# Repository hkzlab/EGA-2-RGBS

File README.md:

# EGA-2-RGBS

Months ago I ran into [this](https://www.youtube.com/watch?v=vwKA1z8tg1g&t=527) video on YouTube that described how to implement an EGA/CGA to analog RGBS signal using just a ROM and a few passive components.
Thinking it was a nice idea, I decided to implement my variant of it (including the tool that generates the values to program the EPROM), also including an optional buffer on the outputs of the ROM.

**CAVEAT EMPTOR:** For now I tested this board only in DOS with a CGA card. Will update this note when I test EGA and colours.

Note that this **will not convert EGA/CGA to VGA**, it will just make the signal analog and compatible with either a SCART input or a scaler like the GBS8200 (tested with [gbs-control](https://github.com/ramapcsx2/gbs-control) firmware).

## Jumpers

- JP1: Bridge if you are using this with an EGA card, remove bridge for CGA
- JP2: Disable Brown colour fix for CGA. No effect on EGA
- JP3: Bridge 1-2 to output a CSYNC signal, bridge 2-3 for /CSYNC

## Building the board

### BOM

- 1x 20pin socket (on U2)
- 1x 32pin wide socket (on U1)
- 2x 100nF ceramic caps (C5 and C4)
- 1x Right angle DB9 female PCB connector (J1)
- 1x 6 or 5 pin screw terminal (J5)
- 1x 2 pin screw terminal (J4)
- 1x 1206 SMD fuse rated around ~100mA (F1), **100mA is already very high for the power consumption of the board, but I had these at hand** 
- 1x 3 pin 2.54mm male pcb header, plus jumper (J3)
- 2x 2 pin 2.54mm male pcb header, plus jumpers (JP1 and JP2)
- 1x First random led you have at hand, optional (D2)
- 1x 1N4733A 5.1v zener diode (D1)
- 1x 74HC244 DIP, optional (U2)
- 1x 27C010 DIP (U1)
- 4x 470 1/4w resistors (R2, R4, R6, R10)
- 3x 1.5k 1/4w resistors (R3, R5, R7)
- 1x 1k 1/4w resistor (R11)
- 2x 4.7k 1/4w resistors (R8, R9)

Remember to program the EPROM with the bin file provided in the repository.

### Building on the cheap

You can omit the following components:

#### Power

Omit F1 and D1, bridge the two connections points of F1. Do this if you trust your power supply and yourself not to make shorts.

You can also omit the power indicator led D2 and its resistor R11

#### Sockets

You can omit both U1 and U2 sockets. Remember to mount C4, C5, R8 and R9 on the underside of the board if you do this.

#### Output buffer

You can omit U2 entirely. Just bridge the following points on the footprint:

- 2->18
- 4->16
- 6->14
- 8->12
- 11->9
- 13->7
- 15->5
- 17->3

Also omit C4 in this case.

## Credits

- [TheRasteri](https://www.youtube.com/channel/UCO1ifHwXHkEyCLFk2b7Z8xA) on YouTube for the original idea

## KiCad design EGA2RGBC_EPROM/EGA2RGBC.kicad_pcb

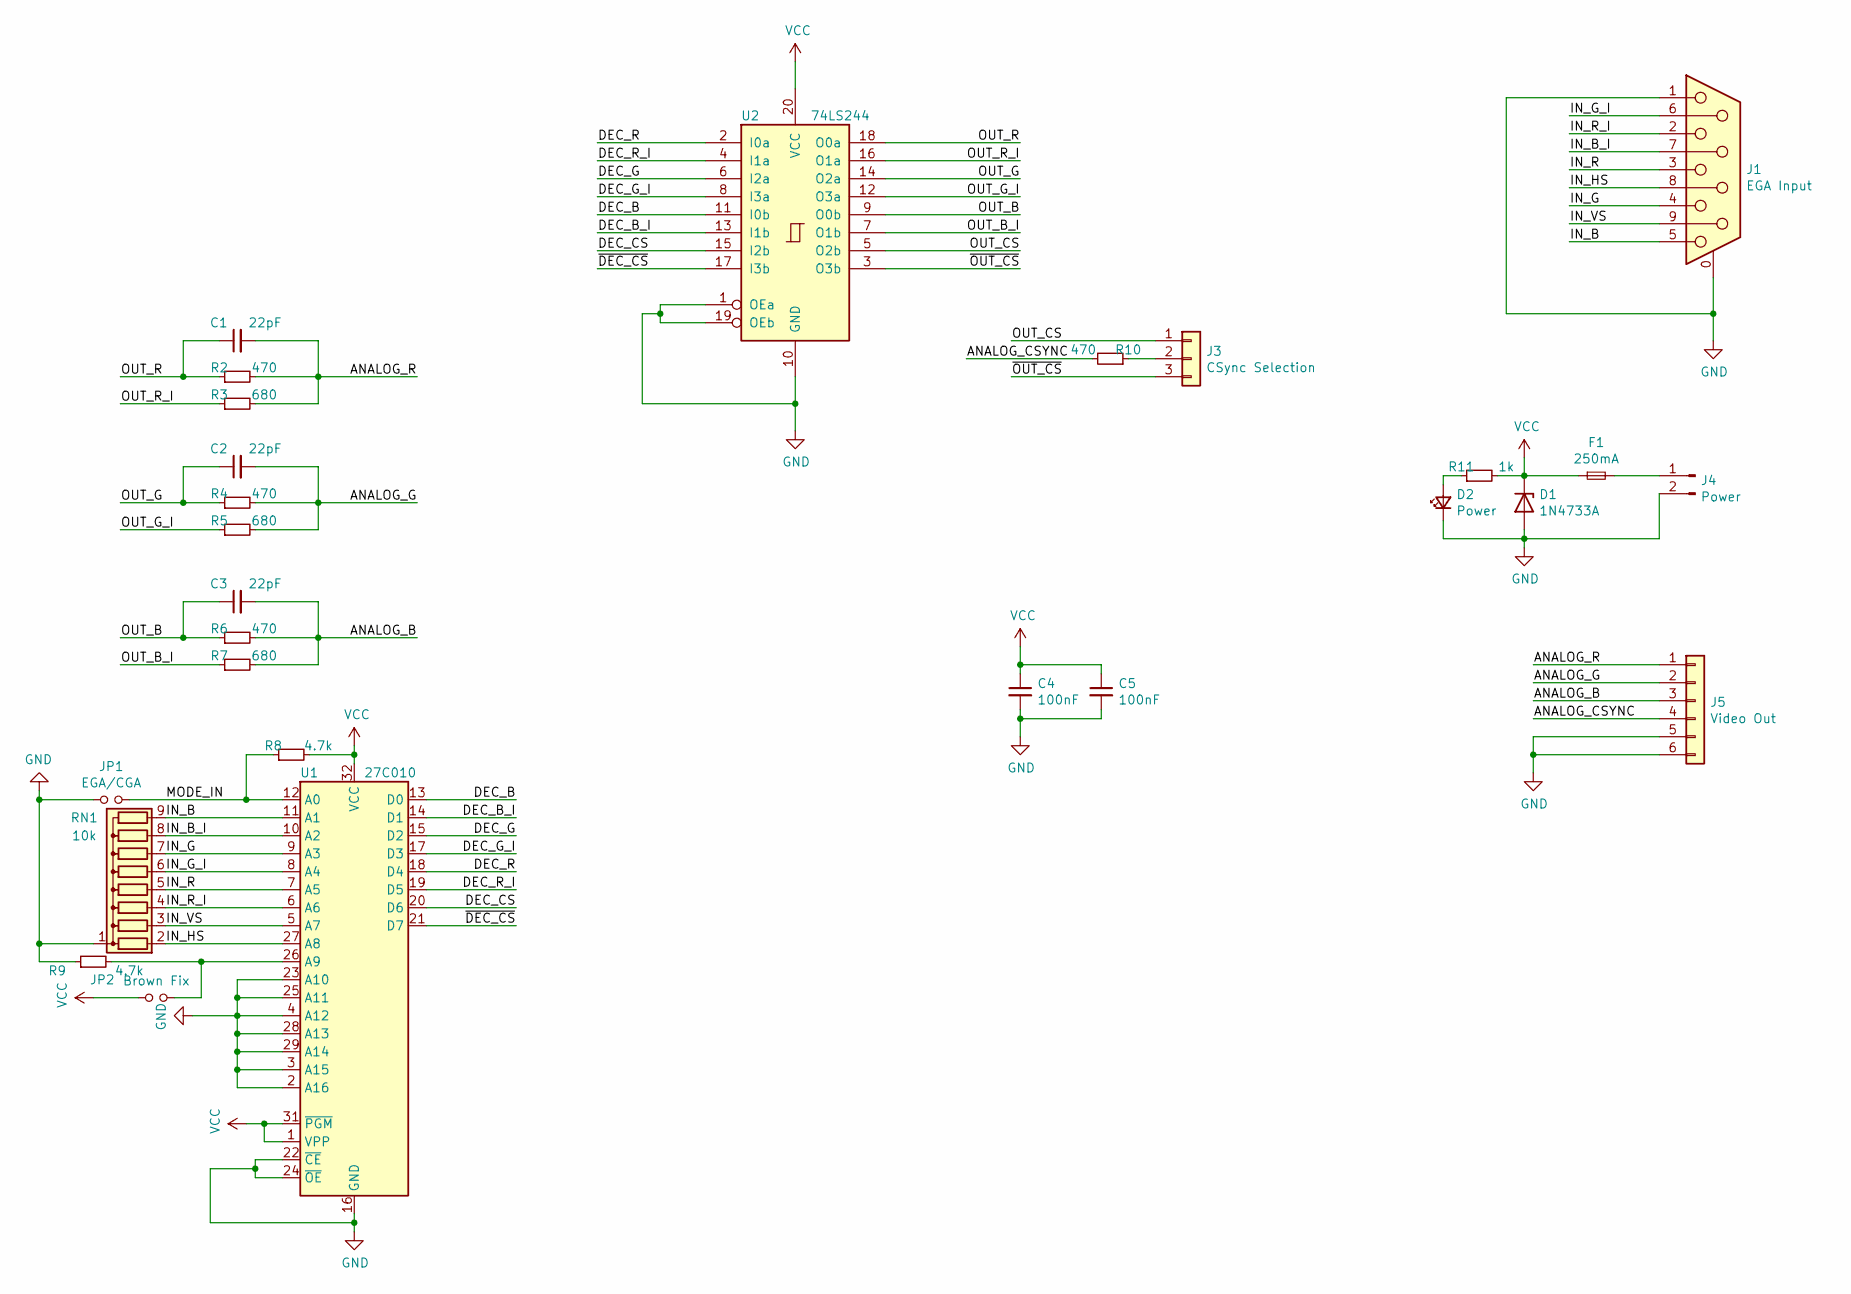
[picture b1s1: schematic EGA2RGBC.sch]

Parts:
C1, C2, C3: 22pF; C_Disc_D3.0mm_W2.0mm_P2.50mm
C4, C5: 100nF; C_Disc_D3.0mm_W2.0mm_P2.50mm
D1: 1N4733A; D_DO-41_SOD81_P10.16mm_Horizontal
D2: Power; LED_D2.0mm_W4.8mm_H2.5mm_FlatTop
F1: 250mA; Fuse_1206_3216Metric
J1: EGA Input; DSUB-9_Female_Horizontal_P2.77x2.84mm_EdgePinOffset4.94mm_H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
J3: CSync Selection; PinSocket_1x03_P2.54mm_Vertical
J4: Power; TerminalBlock_bornier-2_P5.08mm
J5: Video Out; TerminalBlock_bornier-6_P5.08mm
JP1: EGA/CGA; PinHeader_1x02_P2.54mm_Vertical
JP2: Brown Fix; PinHeader_1x02_P2.54mm_Vertical
R2, R4, R6, R10: 470; R_Axial_DIN0204_L3.6mm_D1.6mm_P7.62mm_Horizontal
R3, R5, R7: 680; R_Axial_DIN0204_L3.6mm_D1.6mm_P7.62mm_Horizontal
R8, R9: 4.7k; R_Axial_DIN0204_L3.6mm_D1.6mm_P7.62mm_Horizontal
R11: 1k; R_Axial_DIN0204_L3.6mm_D1.6mm_P7.62mm_Horizontal
RN1: 10k; R_Array_SIP9
U1: 27C010; DIP-32_W15.24mm
U2: 74LS244; DIP-20_W7.62mm

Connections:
/ANALOG_B: C3.2, J5.3, R6.2, R7.2
/ANALOG_CSYNC: J5.4, R10.2
/ANALOG_G: C2.2, J5.2, R4.2, R5.2
/ANALOG_R: C1.2, J5.1, R2.2, R3.2
/DEC_B: U1.13 (D0), U2.11 (I0b)
/DEC_B_I: U1.14 (D1), U2.13 (I1b)
/DEC_CS: U1.20 (D6), U2.15 (I2b)
/DEC_G: U1.15 (D2), U2.6 (I2a)
/DEC_G_I: U1.17 (D3), U2.8 (I3a)
/DEC_R: U1.18 (D4), U2.2 (I0a)
/DEC_R_I: U1.19 (D5), U2.4 (I1a)
/IN_B: J1.5, RN1.9 (R8), U1.11 (A1)
/IN_B_I: J1.7, RN1.8 (R7), U1.10 (A2)
/IN_G: J1.4, RN1.7 (R6), U1.9 (A3)
/IN_G_I: J1.6, RN1.6 (R5), U1.8 (A4)
/IN_HS: J1.8, RN1.2 (R1), U1.27 (A8)
/IN_R: J1.3, RN1.5 (R4), U1.7 (A5)
/IN_R_I: J1.2, RN1.4 (R3), U1.6 (A6)
/IN_VS: J1.9, RN1.3 (R2), U1.5 (A7)
/MODE_IN: JP1.2, R8.1, U1.12 (A0)
/OUT_B: C3.1, R6.1, U2.9 (O0b)
/OUT_B_I: R7.1, U2.7 (O1b)
/OUT_CS: J3.1, U2.5 (O2b)
/OUT_G: C2.1, R4.1, U2.14 (O2a)
/OUT_G_I: R5.1, U2.12 (O3a)
/OUT_R: C1.1, R2.1, U2.18 (O0a)
/OUT_R_I: R3.1, U2.16 (O1a)
/~DEC_CS: U1.21 (D7), U2.17 (I3b)
/~OUT_CS: J3.3, U2.3 (O3b)
GND: C4.2, C5.2, D1.2 (A), D2.1 (K), J1.0 (PAD), J1.1, J4.2, J5.5, J5.6, JP1.1, R9.1, RN1.1 (common), U1.2 (A16), U1.3 (A15), U1.4 (A12), U1.16 (GND), U1.22 (~CE), U1.23 (A10), U1.24 (~OE), U1.25 (A11), U1.28 (A13), U1.29 (A14), U2.1 (OEa), U2.10 (GND), U2.19 (OEb)
unnamed: D2.2 (A), R11.1
unnamed: F1.2, J4.1
unnamed: J3.2, R10.1
unnamed: JP2.2, R9.2, U1.26 (A9)
VCC: C4.1, C5.1, D1.1 (K), F1.1, JP2.1, R8.2, R11.2, U1.1 (VPP), U1.31 (~PGM), U1.32 (VCC), U2.20 (VCC)

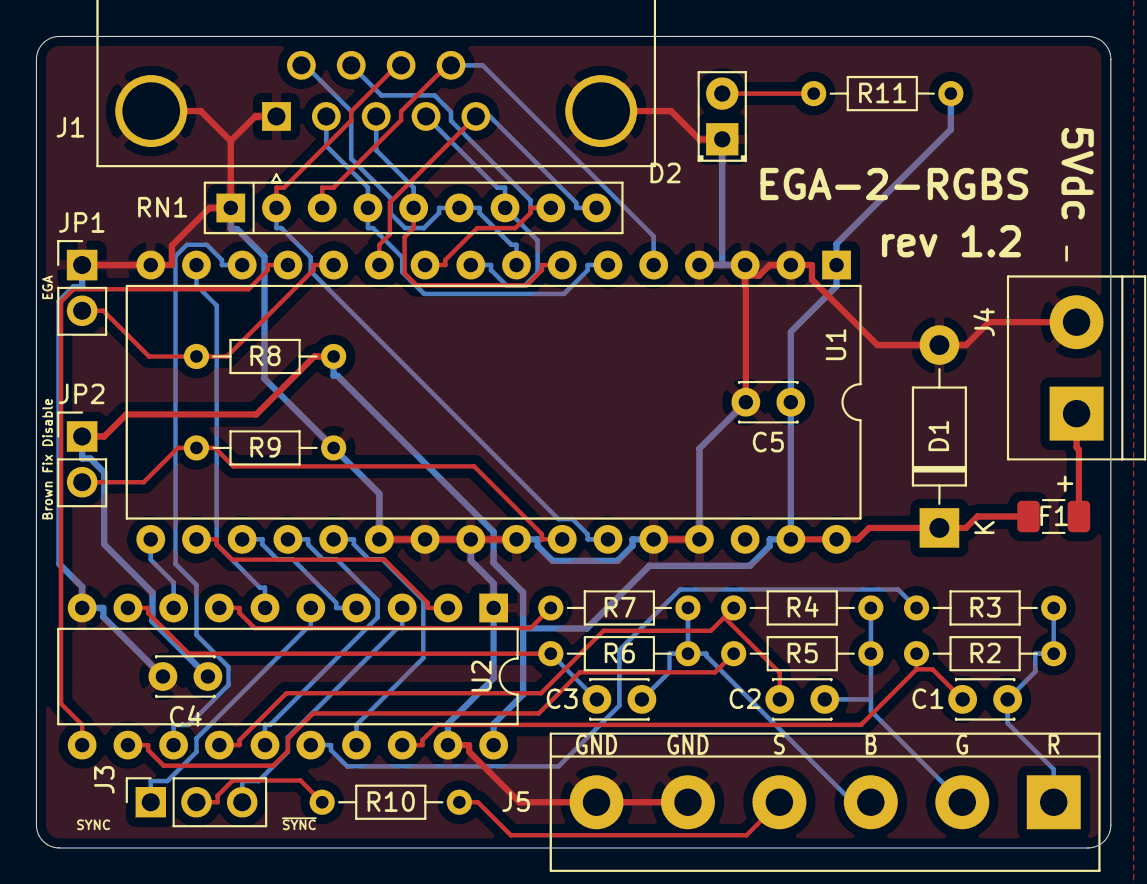
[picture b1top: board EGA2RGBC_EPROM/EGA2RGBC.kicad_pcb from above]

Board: 2 copper layers, 59.7 x 45.1 mm, 27 parts (0 on the bottom side), 35 nets.

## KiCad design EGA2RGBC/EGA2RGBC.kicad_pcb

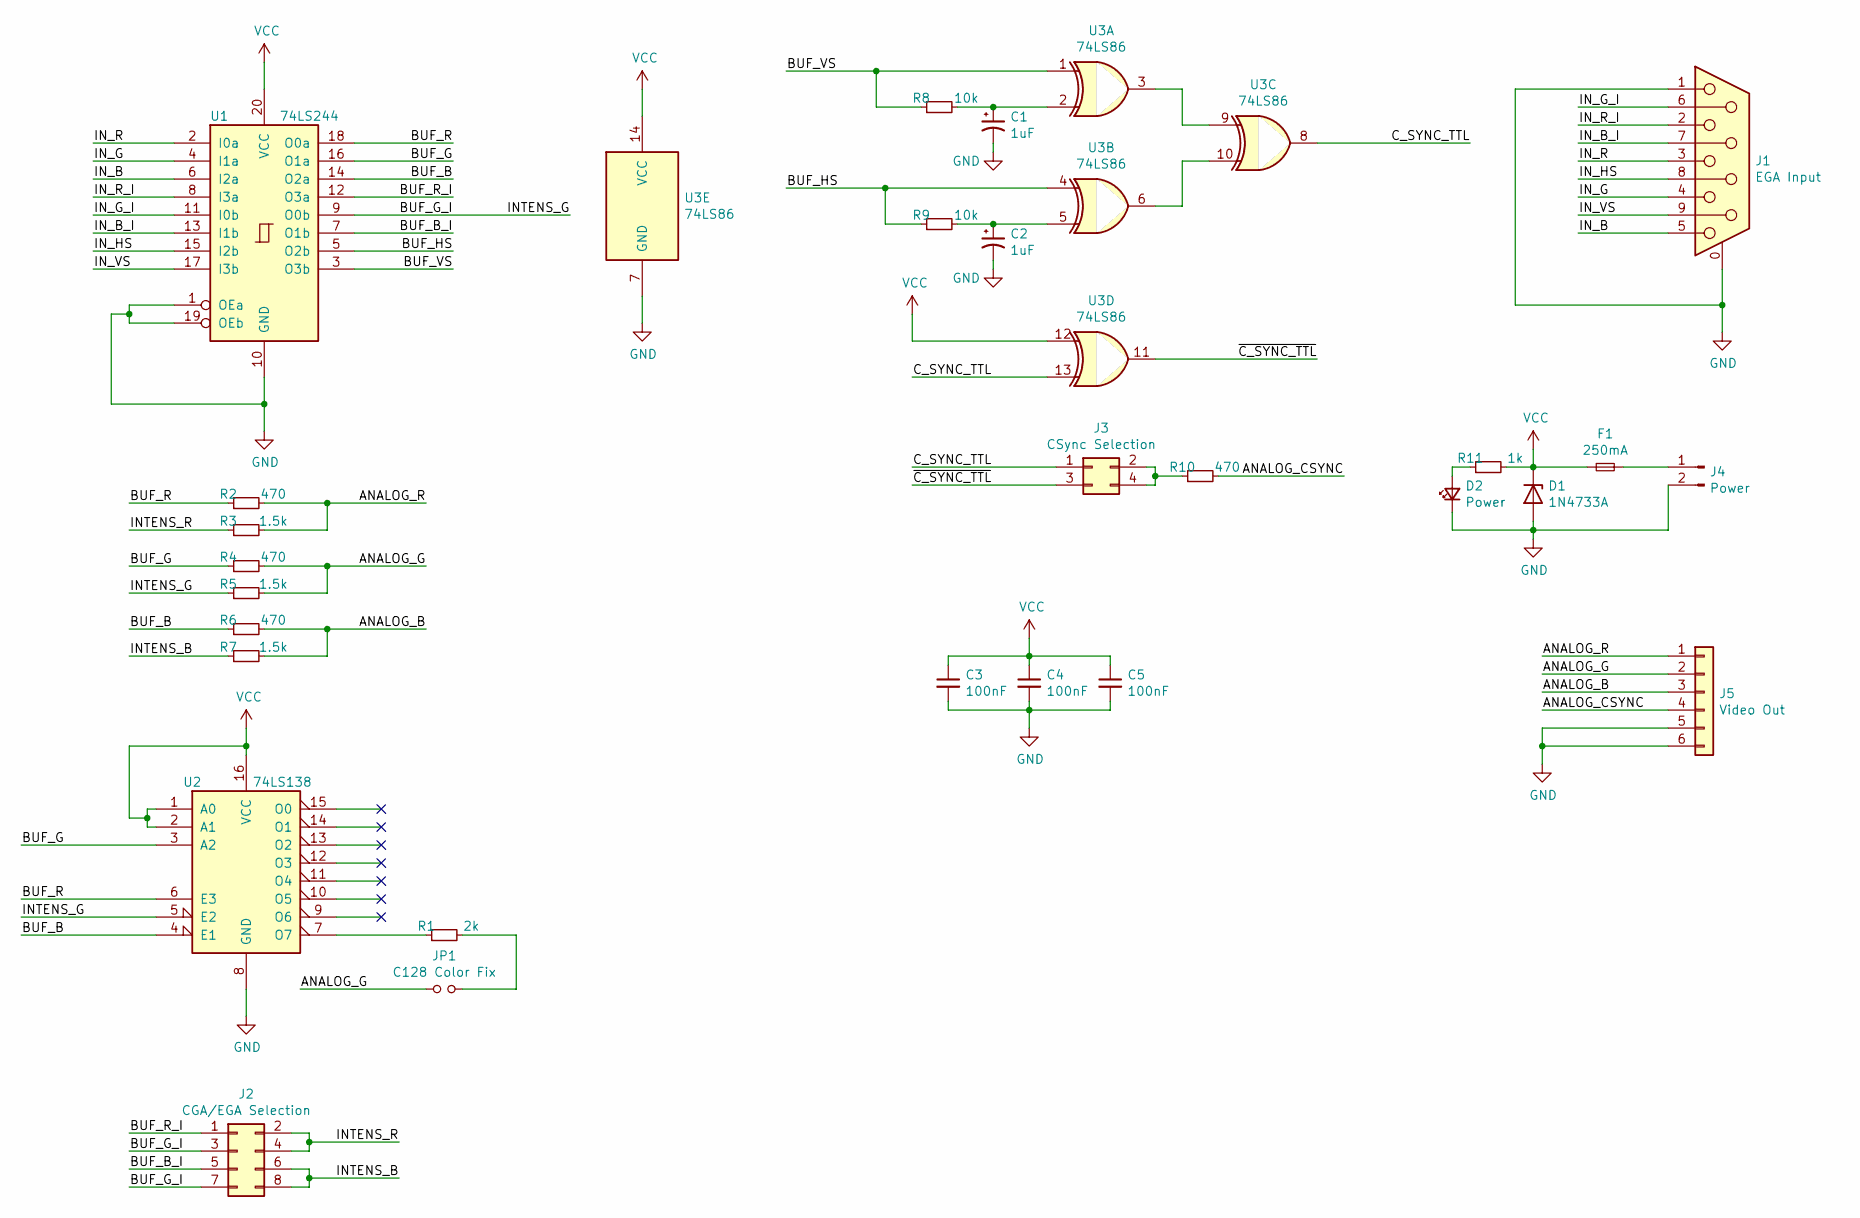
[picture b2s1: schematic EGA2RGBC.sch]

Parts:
C1, C2: 1uF; CP_Radial_D5.0mm_P2.50mm
C3, C4, C5: 100nF; C_Disc_D6.0mm_W2.5mm_P5.00mm
D1: 1N4733A; D_DO-41_SOD81_P10.16mm_Horizontal
D2: Power; LED_D2.0mm_W4.8mm_H2.5mm_FlatTop
F1: 250mA; Fuse_1206_3216Metric
J1: EGA Input; DSUB-9_Female_Horizontal_P2.77x2.84mm_EdgePinOffset4.94mm_H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
J2: CGA/EGA Selection; PinHeader_2x04_P2.54mm_Vertical
J3: CSync Selection; PinHeader_2x02_P2.54mm_Vertical
J4: Power; TerminalBlock_bornier-2_P5.08mm
J5: Video Out; TerminalBlock_bornier-6_P5.08mm
JP1: C128 Color Fix; PinHeader_1x02_P2.54mm_Vertical
R1: 2k; R_Axial_DIN0204_L3.6mm_D1.6mm_P7.62mm_Horizontal
R2, R4, R6, R10: 470; R_Axial_DIN0204_L3.6mm_D1.6mm_P7.62mm_Horizontal
R3, R5, R7: 1.5k; R_Axial_DIN0204_L3.6mm_D1.6mm_P7.62mm_Horizontal
R8, R9: 10k; R_Axial_DIN0204_L3.6mm_D1.6mm_P7.62mm_Horizontal
R11: 1k; R_Axial_DIN0204_L3.6mm_D1.6mm_P7.62mm_Horizontal
U1: 74LS244; DIP-20_W7.62mm
U2: 74LS138; DIP-16_W7.62mm
U3: 74LS86; DIP-14_W7.62mm

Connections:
/ANALOG_B: J5.3, R6.2, R7.2
/ANALOG_CSYNC: J5.4, R10.2
/ANALOG_G: J5.2, JP1.1, R4.2, R5.2
/ANALOG_R: J5.1, R2.2, R3.2
/BUF_B: R6.1, U1.14 (O2a), U2.4 (E1)
/BUF_B_I: J2.5, U1.7 (O1b)
/BUF_G: R4.1, U1.16 (O1a), U2.3 (A2)
/BUF_G_I: J2.3, J2.7, R5.1, U1.9 (O0b), U2.5 (E2)
/BUF_HS: R9.1, U1.5 (O2b), U3.4
/BUF_R: R2.1, U1.18 (O0a), U2.6 (E3)
/BUF_R_I: J2.1, U1.12 (O3a)
/BUF_VS: R8.1, U1.3 (O3b), U3.1
/C_SYNC_TTL: J3.1, U3.8, U3.13
/INTENS_B: J2.6, J2.8, R7.1
/INTENS_R: J2.2, J2.4, R3.1
/IN_B: J1.5, U1.6 (I2a)
/IN_B_I: J1.7, U1.13 (I1b)
/IN_G: J1.4, U1.4 (I1a)
/IN_G_I: J1.6, U1.11 (I0b)
/IN_HS: J1.8, U1.15 (I2b)
/IN_R: J1.3, U1.2 (I0a)
/IN_R_I: J1.2, U1.8 (I3a)
/IN_VS: J1.9, U1.17 (I3b)
/~C_SYNC_TTL: J3.3, U3.11
GND: C1.2, C2.2, C3.2, C4.2, C5.2, D1.2 (A), D2.1 (K), J1.0 (PAD), J1.1, J4.2, J5.5, J5.6, U1.1 (OEa), U1.10 (GND), U1.19 (OEb), U2.8 (GND), U3.7 (GND)
unnamed: C1.1, R8.2, U3.2
unnamed: C2.1, R9.2, U3.5
unnamed: D2.2 (A), R11.1
unnamed: F1.2, J4.1
unnamed: J3.2, J3.4, R10.1
unnamed: JP1.2, R1.2
unnamed: R1.1, U2.7 (O7)
unnamed: U3.3, U3.9
unnamed: U3.6, U3.10
VCC: C3.1, C4.1, C5.1, D1.1 (K), F1.1, R11.2, U1.20 (VCC), U2.1 (A0), U2.2 (A1), U2.16 (VCC), U3.12, U3.14 (VCC)

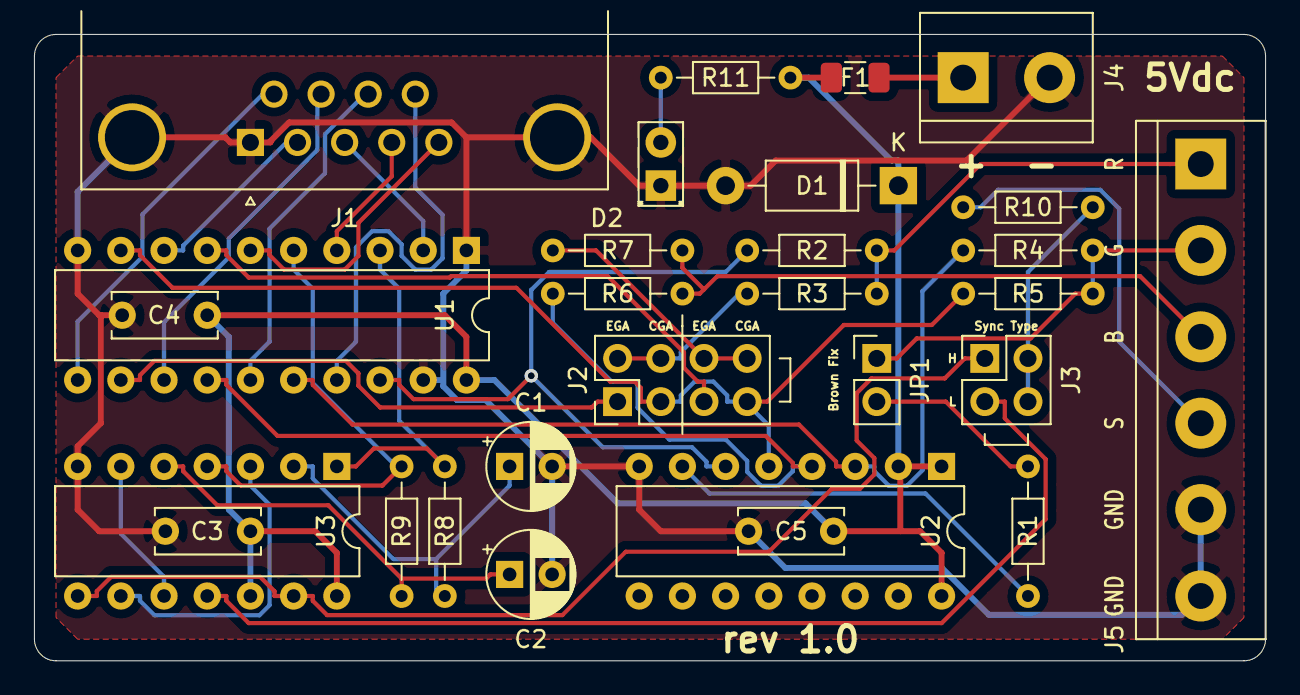
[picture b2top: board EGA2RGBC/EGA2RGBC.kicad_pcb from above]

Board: 2 copper layers, 72.4 x 36.8 mm, 28 parts (0 on the bottom side), 35 nets.

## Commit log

2020-11-26 Schematics for EGA to RGB
2020-11-26 Added footprints
2020-11-26 Fix labels and generate gerbers
2020-11-26 Update PCB
2020-11-26 Add EGA2RGBC eprom version
2020-11-27 Update schematics
2020-11-27 Moved resistors
2020-11-27 Add eprom bin
2021-01-10 Removed EPROMless version
2021-01-10 Add rev 1.1 files
2021-01-10 Add README
2021-01-10 Add ROMGen
2021-01-10 More README info
2021-01-10 Rename header in README
2021-01-11 Add license files
2021-08-16 Added caps on color lines
2021-08-26 Add code to generate combinations for brownfix
2021-08-26 Add code to generate table with brownfix also
2021-08-26 Additional code to the image creation
2021-08-26 Updated README to include new table
2021-09-07 Change some resistor values
2021-09-08 Add code to do brown fix with EGA
2021-09-08 Add pulldown resistor to inputs
2021-09-08 Add new revision of board
2021-11-09 Update KiCad URL
